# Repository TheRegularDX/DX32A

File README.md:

# DX32A DELUXE
This is the base DX32 model. The DX32A DELUXE is a custom development board based on the Espressif ESP32S3 N16R8 WiFi and Bluetooth module. designed to be simple and breadboard compatible

## Features
- WiFi and BLE
- x25 GPIO pins
- x1 WS2812B addresable RGB led
- x1 MicroSD card reader

## PlatformIO support
Ive added to this repo a slightly modified version of the official S3 DevKitC .json file to this repo, drag and drop it into `.platformio/platforms/espressif32/boards` to add the DX32 to the PlatformIO boards selector, this can also be used with any other board based on the ESP32S3 N16R8

## Faq
>why it name delucks?

just because i think deluxe is a cool word in general.

## Name change
As of 31/3/24 this board has been renamed to just "DELUXE" instead of "DELUXE Mini", the latter will be reused for a future board

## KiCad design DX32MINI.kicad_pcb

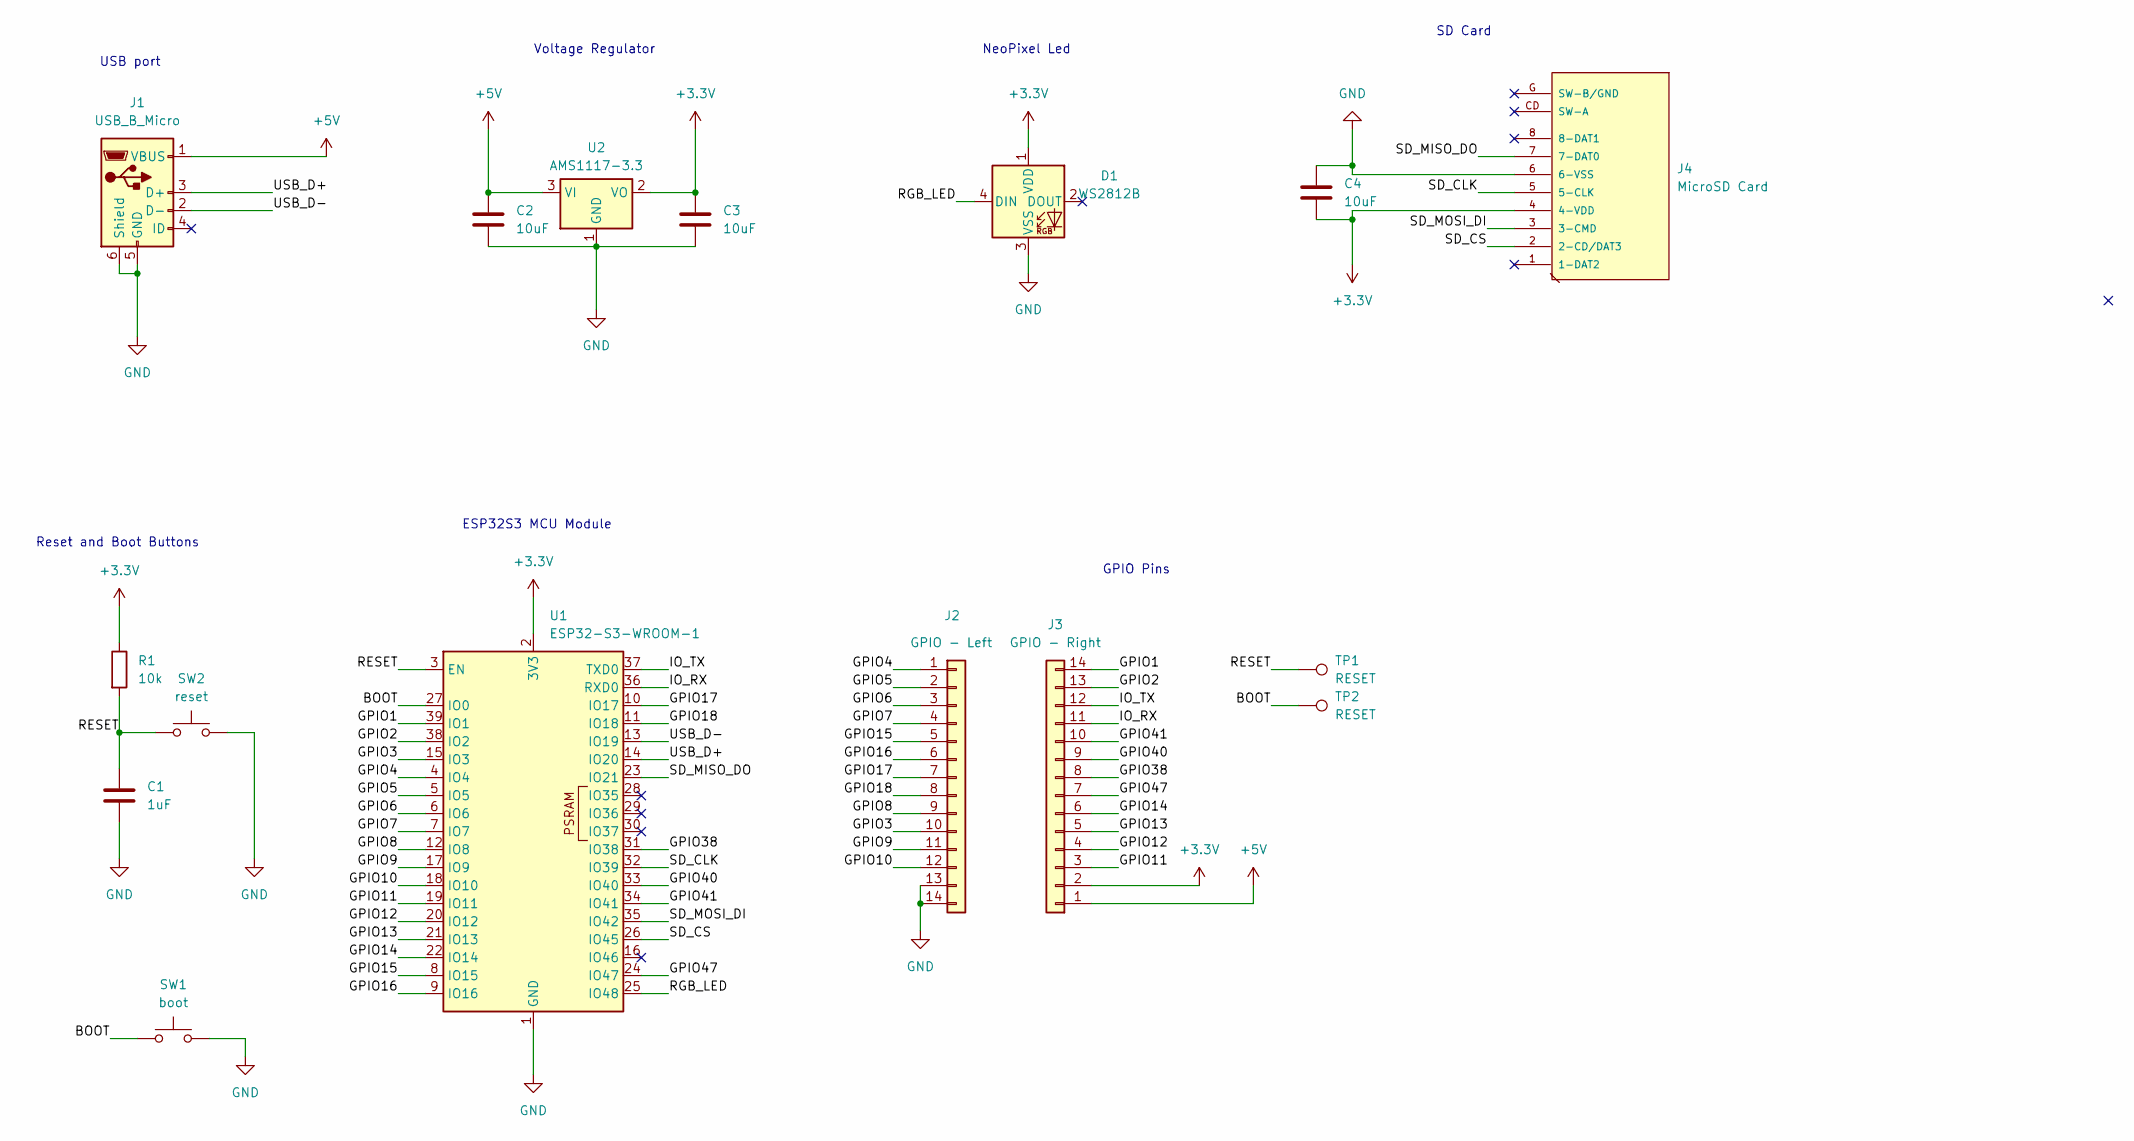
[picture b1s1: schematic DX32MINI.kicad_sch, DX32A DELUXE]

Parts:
C1: 1uF; C_0805_2012Metric_Pad1.18x1.45mm_HandSolder
C2, C3, C4: 10uF; C_0805_2012Metric_Pad1.18x1.45mm_HandSolder
D1: WS2812B; LED_WS2812B_PLCC4_5.0x5.0mm_P3.2mm
J1: USB_B_Micro; USB_Micro-B_Molex-105017-0001
J2: GPIO - Left; PinHeader_1x14_P2.54mm_Vertical
J3: GPIO - Right; PinHeader_1x14_P2.54mm_Vertical
J4: MicroSD Card; 112J-TDAR-R01
R1: 10k; R_0805_2012Metric_Pad1.20x1.40mm_HandSolder
SW1: boot; SW_Push_SPST_NO_Alps_SKRK
SW2: reset; SW_Push_SPST_NO_Alps_SKRK
TP1, TP2: RESET; TestPoint_Pad_1.5x1.5mm
U1: ESP32-S3-WROOM-1
U2: AMS1117-3.3; SOT-223-3_TabPin2

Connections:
+3.3V: C3.1, C4.2, D1.1 (VDD), J3.2, J4.4 (4-VDD), R1.1, U1.2 (3V3), U2.2 (VO)
+5V: C2.1, J1.1 (VBUS), J3.1, U2.3 (VI)
/BOOT: SW1.1, TP2.1, U1.27 (IO0)
/GPIO1: J3.14, U1.39 (IO1)
/GPIO2: J3.13, U1.38 (IO2)
/GPIO3: J2.10, U1.15 (IO3)
/GPIO4: J2.1, U1.4 (IO4)
/GPIO5: J2.2, U1.5 (IO5)
/GPIO6: J2.3, U1.6 (IO6)
/GPIO7: J2.4, U1.7 (IO7)
/GPIO8: J2.9, U1.12 (IO8)
/GPIO9: J2.11, U1.17 (IO9)
/GPIO10: J2.12, U1.18 (IO10)
/GPIO11: J3.3, U1.19 (IO11)
/GPIO12: J3.4, U1.20 (IO12)
/GPIO13: J3.5, U1.21 (IO13)
/GPIO14: J3.6, U1.22 (IO14)
/GPIO15: J2.5, U1.8 (IO15)
/GPIO16: J2.6, U1.9 (IO16)
/GPIO17: J2.7, U1.10 (IO17)
/GPIO18: J2.8, U1.11 (IO18)
/GPIO38: J3.8, U1.31 (IO38)
/GPIO40: J3.9, U1.33 (IO40)
/GPIO41: J3.10, U1.34 (IO41)
/GPIO47: J3.7, U1.24 (IO47)
/IO_RX: J3.11, U1.36 (RXD0)
/IO_TX: J3.12, U1.37 (TXD0)
/RESET: C1.1, R1.2, SW2.1, TP1.1, U1.3 (EN)
/RGB_LED: D1.4 (DIN), U1.25 (IO48)
/SD_CLK: J4.5 (5-CLK), U1.32 (IO39)
/SD_CS: J4.2 (2-CD/DAT3), U1.26 (IO45)
/SD_MISO_DO: J4.7 (7-DAT0), U1.23 (IO21)
/SD_MOSI_DI: J4.3 (3-CMD), U1.35 (IO42)
/USB_D+: J1.3 (D+), U1.14 (IO20)
/USB_D-: J1.2 (D-), U1.13 (IO19)
GND: C1.2, C2.2, C3.2, C4.1, D1.3 (VSS), J1.5 (GND), J1.6 (Shield), J2.13, J2.14, J4.6 (6-VSS), SW1.2, SW2.2, U1.1 (GND), U1.40 (GND), U1.41 (GND), U2.1 (GND)

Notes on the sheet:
ESP32S3 MCU Module
Voltage Regulator
SD Card
GPIO Pins
USB port
NeoPixel Led
Reset and Boot Buttons

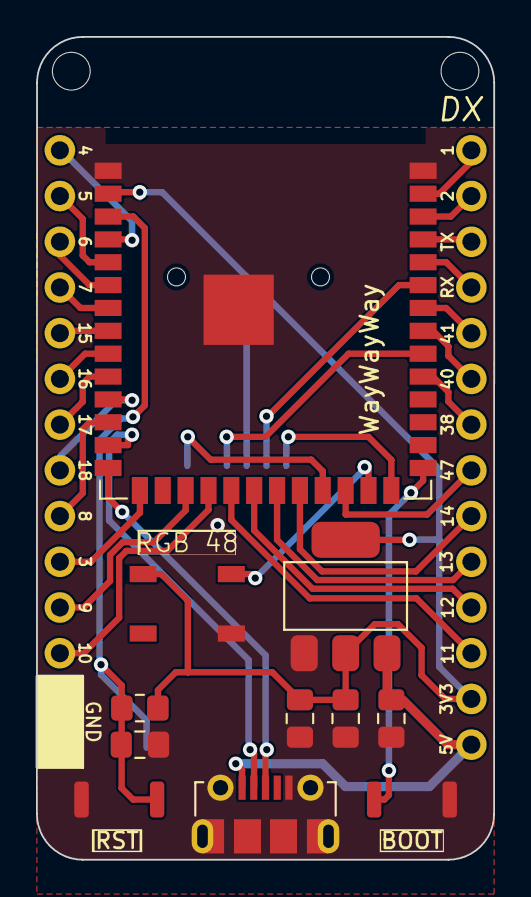
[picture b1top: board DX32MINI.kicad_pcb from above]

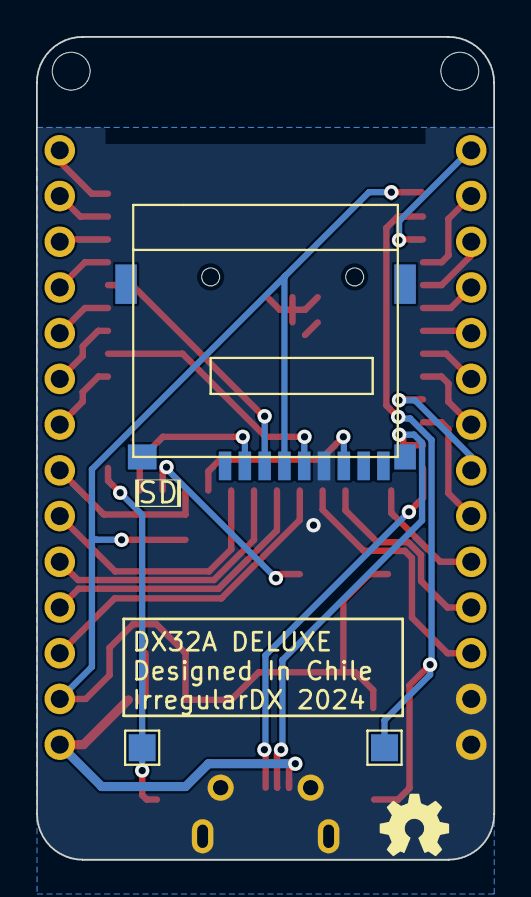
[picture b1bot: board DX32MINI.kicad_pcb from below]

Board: 2 copper layers, 25.4 x 45.7 mm, 18 parts (3 on the bottom side), 36 nets.

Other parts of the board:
anotherhole: MountingHole_2.1mm
hole: MountingHole_2.1mm

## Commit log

2024-03-22 updated board to revision 1.2
2024-03-22 updated file
2024-03-26 Create DX32_DELUXE_ESP32S3.json
    added file for plattformio usage
2024-04-17 Rename LICENSE.txt to LICENSE
